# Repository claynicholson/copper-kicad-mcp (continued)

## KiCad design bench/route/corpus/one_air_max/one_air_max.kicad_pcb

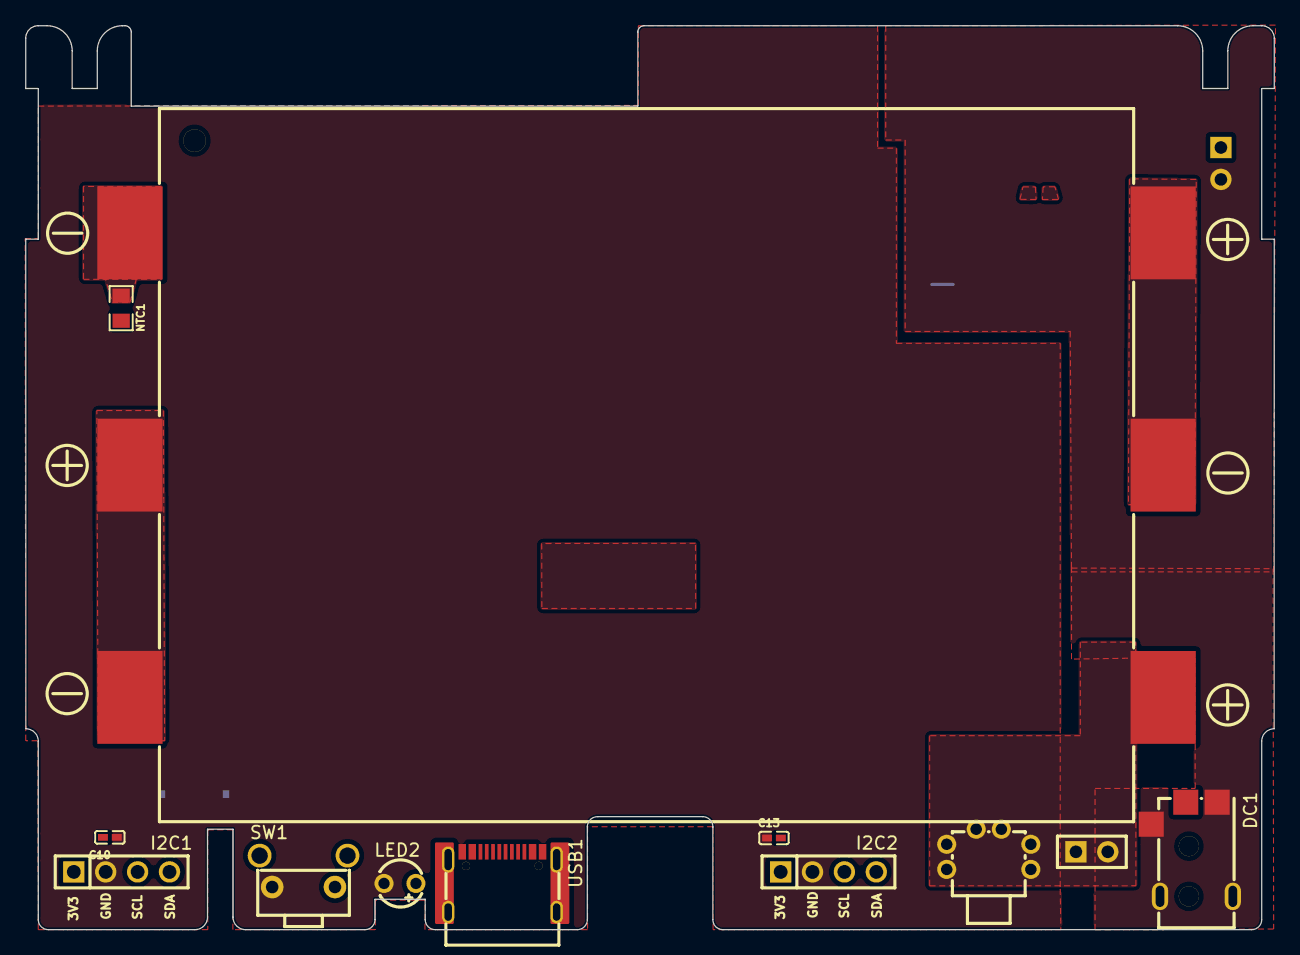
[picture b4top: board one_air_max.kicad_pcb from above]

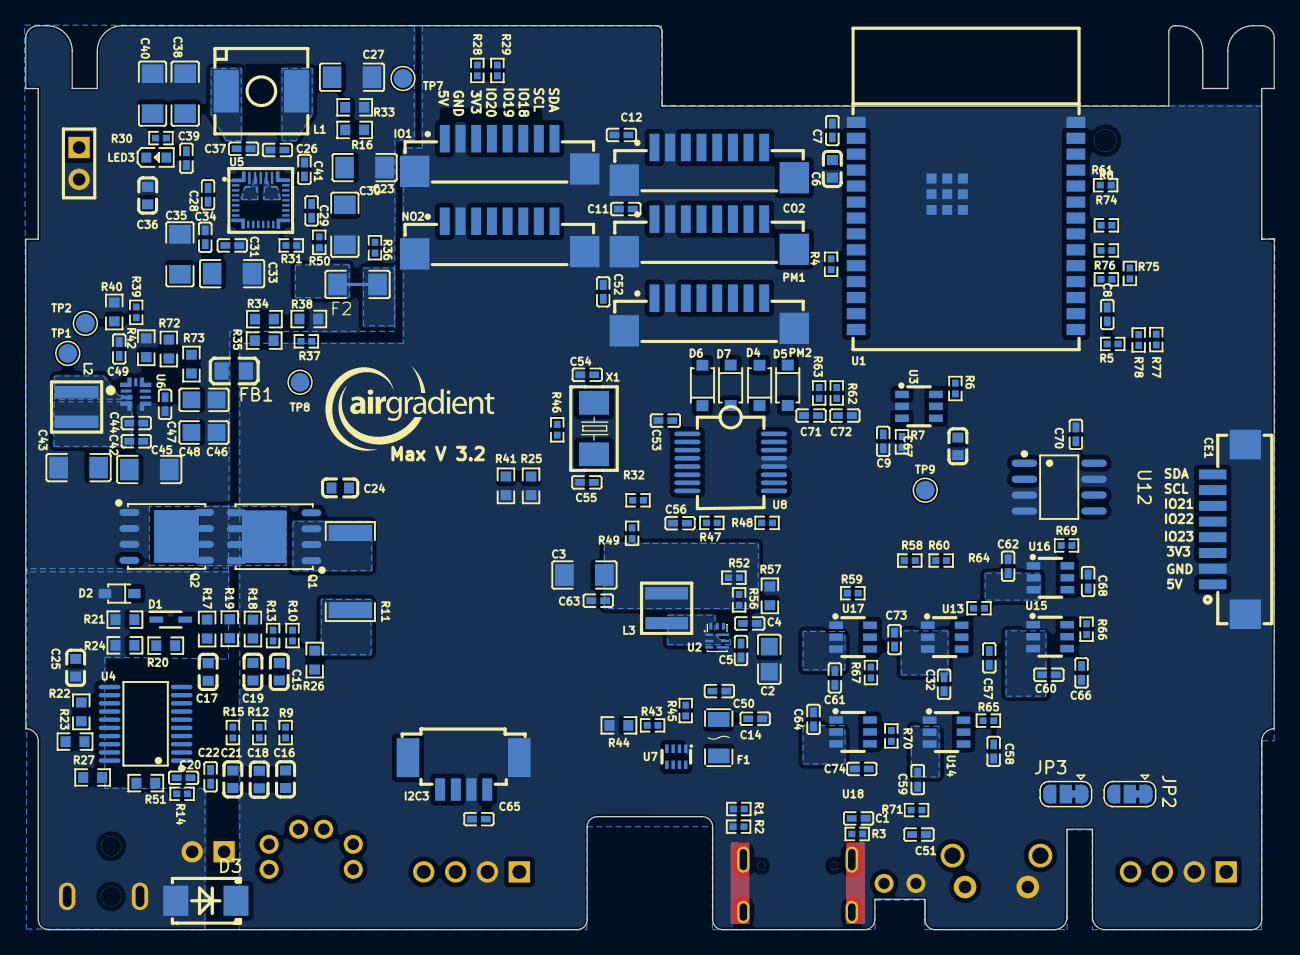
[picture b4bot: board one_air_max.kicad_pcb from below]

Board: 4 copper layers, 99.5 x 72.0 mm, 204 parts (192 on the bottom side), 120 nets, no tracks yet.

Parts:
BAT1: BH-18650-B5BA016; BAT-SMD_BH-18650-B5BA016
Battery1: ZX-PM2.54-1-2PY; HDR-TH_2P-P2.54-V-F
C1, C5, C7, C9, C10, C11, C12, C13, C26, C31, C34, C37, C39, C42, C44, C47, C50, C51, C52, C53, C56, C63, C65, C70: 0.1uF; C0402
C2: 10uF/25V; C0805
C3: 22uF/16V; C1206
C4, C49: 3.3nF; C0402
C6: 22uF; C0603
C8: 10nF; C0402
C14, C57, C58, C68, C74: 22uF; C0402
C15, C16, C17, C18, C19, C21, C24, C25: 0.1uF/50V; C0603
C20, C22: 1uF/50V; C0402
C23, C27, C30, C33, C35, C38, C40, C43, C45: 10uF; C1206
C28, C29: 47nF; C0402
C32, C59, C60, C61, C62, C64: 2.2uF; C0402
C36: 4.7uF; C0603
C41, C71, C72: 1nF; C0402
C46, C48: 22uF; C0805
C54, C55: 22pF_NM; C0402
C66, C73: 1uF; C0402
C67: 500pF; C0603
CE1: HC-1.25-8PWT; CONN-SMD_HC-1.25-8PWT
CO2: HC-1.25-8PLT; CONN-SMD_8P-P1.25_HC-1.25-8PLT
D1: BAS16J_135; SOD2512X80N
D2: MMSZ5246BS-7-F; SOD-323_L1.8-W1.3-LS2.5-RD
D3: SMBJ24A_C908801; SMB_L4.4-W3.6-LS5.3-RD
D4, D5, D6, D7: B5817W_C7420328; SOD-123_L2.7-W1.6-LS3.7-FD
DC1: DC-045A-13A; DC-IN-SMD_DC-045A-13A
F1: 2A-16V; F1206
F2: Fuse 5A; PCB_fuse
FB1: PBY201209T-601Y-N; L0805
I2C1, I2C2: Conn_01x04; HDR-TH_4P-P2.54-V-F
I2C3: 1.25-4PWB; CONN-SMD_1.25-4PWB
IO1: HC-1.25-8PLT; CONN-SMD_8P-P1.25_HC-1.25-8PLT
JP2, JP3: SolderJumper_3_Bridged12; SolderJumper-3_P1.3mm_Bridged12_RoundedPad1.0x1.5mm
L1: SPM6530T-1R0M120; IND-SMD_L7.1-W6.5-P5.60
L2: XGL4020-102MEC; IND-SMD_L4.0-W4.0_XAL4030-332MEC
L3: YSMC0420V-1R0M; IND-SMD_L4.0-W4.0_XGL4020
LED2: XL-304UBC; LED-TH_BD3.8-P2.54-FD_BLUE
LED3: FC-DA1608HRK-620D; LED0603-RD_RED
NO2: HC-1.25-8PLT; CONN-SMD_8P-P1.25_HC-1.25-8PLT
NTC1: KNTC0805/10KF3950; R0805
PM1, PM2: HC-1.25-8PLT; CONN-SMD_8P-P1.25_HC-1.25-8PLT
PWR_SW1: TK-6580A8-1; SW-TH_TK-6580A8-1
Q1, Q2: CSD18534Q5A; PQFN-8_L5.8-W4.9-P1.27-LS6.0-BL
R1, R2, R48: 5.1K; R0402
R3, R6, R31, R37: 100K; R0402
R4, R5, R8, R28, R29, R30, R32, R45, R47, R49, R50, R58, R59, R60, R61, R64, R65, R66, R67, R69, R70, R74, R75, R76, R77, R78: 10K; R0402
R7: 51K; R0402
R9, R12, R14, R15: 1K; R0402
R10, R13, R36: 100; R0402
R11: 10m / 1W; R2512
R16: 10.5K; R0603
R17, R19: 5.1K; R0603
R18: 10M; R0603
R20: 1M; R0603
R21: 3M; R0603
R22: 10K; R0603
R23, R25, R26, R27, R33, R41, R51, R72, R73: 0; R0603
R24: 470K; R0603
R34: 5.23K; R0603
R35: 255K; R0603
R38: 30.1K; R0603
R39: 200K; R0402
R40: 27K; R0603
R42, R57: 7.15K; R0603
R43: 16.9K; R0402
R44: 5K; R0603
R46: 1M; R0402
R52: 113k; R0402
R56: 24.9k; R0402
R62, R63: 22; R0402
R71: 210; R0402
SW1: TS-1096-A1B2-D2; KEY-TH_TS-1096-A1B2-D2
Solarpower1: ZX-PM2.54-1-2PY; HDR-TH_2P-P2.54-V-F
TP1, TP2, TP7, TP8, TP9: T_PG; TestPoint_Pad_D1.5mm
U1: ESP32-C6-WROOM-1-N8; WIRELM-SMD_ESP32-C6-WROOM-1
U2: TPS62902RPJR; VQFN-HR-9_L2.0-W1.5-P0.50-TL
U3: TPL5010DDCR; SOT-23-6_L2.9-W1.6-P0.95-LS2.8-BR
U4: BQ7790512PWR; TSSOP-20_L6.5-W4.4-P0.65-LS6.4-BL
U5: BQ25672RQMR; VQFN-29_L4.0-W4.0-P0.40-BL
U6: TPS62903QRYTRQ1_C20345985; VQFNHR-9_L2.2-W2.0_TPS62993QRYTRQ1
U7: TPS2117DRLR_C22399676; SOT-583-8_L2.1-W1.2-P0.50-LS1.6-BL
U8: WK2132-ISSG; SSOP-16_L7.2-W5.3-P0.65-LS7.8-BL
U12: AT24CM02-SSHD-B; SOIC-8_L4.9-W3.9-P1.27-LS6.0-BL
U13, U14, U15, U16, U17, U18: TPS27081ADDCR; SOT-23-6_L2.9-W1.6-P0.95-LS2.8-BR
USB1: GT-USB-7010ASV; USB-C-SMD_G-SWITCH_GT-USB-7010ASV
X1: SMD-5032_2P 14.7456MHZ 20PF 20PPM; OSC-SMD_L5.0-W3.2

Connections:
+3V3: C3.2, C6.2, C7.2, C9.1, C10.2, C13.2, C53.2, C63.2, C65.2, C66.2, C70.2, C73.2, I2C1.1, I2C2.1, I2C3.1, IO1.3, L3.1, R4.2, R5.2, R6.1, R8.2, R28.2, R29.2, R32.2, R47.2, R48.1, R49.2, R52.2, R66.2, R67.2, R74.2, R75.2, R76.2, R77.2, R78.2, U1.2 (3V3), U2.3 (VOS), U3.1 (VDD), U8.1 (VCC), U12.8 (VCC), U15.4 (VIN), U17.4 (VIN)
+5V: C2.1, C5.2, C14.2, C50.2, C57.2, C58.2, C68.2, C74.2, F1.1, IO1.1, R45.2, R64.2, R65.2, R69.2, R70.2, U2.5 (EN), U2.6 (VIN), U13.4 (VIN), U14.4 (VIN), U16.4 (VIN), U18.4 (VIN)
+5VBAT: C42.2, C43.2, C44.2, C45.2, L2.1, R39.2, U6.3 (VOS), U7.6 (VIN2)
+5VUSB: R43.2, U7.3 (VIN1), U7.5 (MODE), USB1.A4B9 (VBUS), USB1.B4A9 (VBUS)
/A0: R25.1, U8.6 (MP1)
/A1: R41.1, U8.4 (MP3)
/BOOT: C8.2, R5.1, SW1.1, U1.15 (IO9)
/Battery_holder/AVDD: C22.2, R23.2, U4.2 (AVDD)
/Battery_holder/BAT1: BAT1.2, BAT1.4, R9.1
/Battery_holder/BAT2: BAT1.3, BAT1.5, R12.1
/Battery_holder/BAT_TH: NTC1.2, R22.1, U4.15 (TS)
/Battery_holder/CHG: R19.2, U4.13 (CHG)
/Battery_holder/CTRC: R26.1, U4.18 (CTRC)
/Battery_holder/CTRD: R27.2, U4.19 (CTRD)
/Battery_holder/DSG: R17.2, U4.11 (DSG)
/Battery_holder/LD: R24.2, U4.14 (LD)
/Battery_holder/SRN: C17.1, C19.2, R13.2, U4.10 (SRN)
/Battery_holder/SRP: C15.2, C17.2, R10.2, U4.9 (SRP)
/Battery_holder/VBAT+: BAT1.6, C25.2, PWR_SW1.4, PWR_SW1.6, R14.1, R15.1
/EN: C67.2, R6.2, TP9.1, U1.3 (EN), U3.6 (RSTn)
/EN_CE: CE1.5, R61.2, U1.23 (IO15), U15.5 (ON/OFF), U16.5 (ON/OFF)
/EN_CO2: R58.2, U1.5 (IO5), U14.5 (ON/OFF)
/EN_NO2: R59.2, U1.4 (IO4), U17.5 (ON/OFF), U18.5 (ON/OFF)
/EN_PM: R60.2, U1.26 (IO3), U13.5 (ON/OFF)
/I2C_~RST: C56.2, R47.1, U8.8 (#RSTN)
/IO18: IO1.6, R78.1, U1.16 (IO18)
/IO19: IO1.5, R77.1, U1.17 (IO19)
/IO20: IO1.4, R76.1, U1.18 (IO20)
/IO21: CE1.6, R75.1, U1.19 (IO21)
/IO22: R74.1, U1.20 (IO22)
/IO23: CE1.4, R8.1, U1.21 (IO23)
/LED: R71.2, U1.11 (IO10)
/PM1_RXD: D5.2 (K), PM1.5
/PM1_TXD: D4.1 (A), PM1.4
/PM2_RXD: D7.2 (K), PM2.5
/PM2_TXD: D6.1 (A), PM2.4
/PR1: R43.1, R44.2, U7.4 (PR1)
/RX_CE: JP3.1 (A), U1.24 (RXD0)
/RX_CO2: CO2.5, U1.8 (IO0)
/SCL: I2C1.3, I2C2.3, I2C3.3, IO1.7, JP2.3 (B), NO2.7, R28.1, R32.1, U1.6 (IO6), U5.14 (SCL), U8.5 (MP2), U12.6 (SCL)
/SCL_TXD: CE1.7, JP2.2 (C)
/SDA: I2C1.4, I2C2.4, I2C3.4, IO1.8, JP3.3 (B), NO2.8, R29.1, R49.1, U1.7 (IO7), U5.15 (SDA), U8.7 (MP0), U12.5 (SDA)
/SDA_RXD: CE1.8, JP3.2 (C)
/Solar_module/BTST1: C28.2, U5.4 (BTST1)
/Solar_module/BTST2: C29.2, U5.19 (BTST2)
/Solar_module/FB/VSET: R39.1, R40.2, TP2.1, U6.9 (FB/VSET)
/Solar_module/ILIM_HIZ: R35.2, R37.2, U5.17 (ILIM_HIZ)
/Solar_module/PROG: R16.2, U5.20 (PROG)
/Solar_module/REGN: C36.2, R34.1, R35.1, U5.5 (REGN)
/Solar_module/SW1: C28.1, L1.1, U5.28 (SW1)
/Solar_module/SW2: C29.1, L1.2, U5.26 (SW2)
/Solar_module/SYS: C26.2, C27.2, R72.1, TP7.1, U5.25 (SYS)
/Solar_module/Solar+: C31.2, C33.2, C34.2, C35.2, D3.1, DC1.1, R30.1, Solarpower1.1, U5.2 (VBUS), U5.3 (VBUS), U5.8 (VAC2), U5.9 (VAC1)
/Solar_module/VBAT: Battery1.1, C23.2, C30.2, F2.1, R36.2, R73.1, TP8.1, U5.22 (BAT), U5.23 (BAT)
/TX_CE: JP2.1 (A), U1.25 (TXD0)
/TX_CO2: CO2.4, U1.9 (IO1)
/USB+: R63.2, U1.14 (IO13)
/USB-: R62.2, U1.13 (IO12)
/USB_D+: C71.2, R63.1, USB1.A6 (DP1), USB1.B6 (DP2)
/USB_D-: C72.2, R62.1, USB1.A7 (DN1), USB1.B7 (DN2)
/VMUX: F1.2, U7.2 (VOUT), U7.7 (VOUT)
/VOUT1: C11.2, C32.2, C52.2, PM1.1, PM2.1, U13.2 (VOUT), U13.3 (VOUT)
/VOUT2: C12.2, C59.2, CO2.1, U14.2 (VOUT), U14.3 (VOUT)
/VOUT3: C60.2, CE1.3, U15.2 (VOUT), U15.3 (VOUT)
/VOUT4: C62.2, CE1.1, U16.2 (VOUT), U16.3 (VOUT)
/VOUT5: C61.2, NO2.3, U17.2 (VOUT), U17.3 (VOUT)
/VOUT6: C64.2, NO2.1, U18.2 (VOUT), U18.3 (VOUT)
/WD_RST: U1.27 (IO2), U3.4 (DONE)
BAT-: BAT1.1, C15.1, C16.1, C18.1, C19.1, C20.1, C21.1, C22.1, NTC1.1, R10.1, R11.1, R26.2, R27.1, R51.1, U4.8 (AVSS), U4.20 (DVSS)
GND: C1.1, C2.2, C3.1, C4.1, C5.1, C6.1, C7.1, C8.1, C9.2, C10.1, C11.1, C12.1, C13.1, C14.1, C32.1, C50.1, C51.1, C52.1, C53.1, C54.1, C55.1, C56.1, C57.1, C58.1, C59.1, C60.1, C61.1, C62.1, C63.1, C64.1, C65.1, C66.1, C67.1, C68.1, C70.1, C71.1, C72.1, C73.1, C74.1, CE1.2, CE1.9, CE1.10, CO2.2, CO2.10, FB1.1, I2C1.2, I2C2.2, I2C3.2, I2C3.5, IO1.2, IO1.9, IO1.10, LED2.2 (K), NO2.2, NO2.9, NO2.10, PM1.2, PM1.10, PM2.2, PM2.9, PM2.10, R1.1, R2.1, R3.1, R7.1, R25.2, R41.2, R44.1, R56.1, R57.1, R58.1, R59.1, R60.1, R61.1, SW1.2, U1.1 (GND), U1.28 (GND), U1.29 (GND), U1.30 (GND), U1.31 (GND), U1.32 (GND), U1.33 (GND), U1.34 (GND), U1.35 (GND), U1.36 (GND), U1.37 (GND), U2.4 (GND), U3.2 (GND), U7.1 (GND), U8.12 (GND), U8.13 (MD0), U12.3 (A2), U12.4 (GND), U12.7 (WP), U13.1 (R2), U14.1 (R2), U15.1 (R2), U16.1 (R2), U17.1 (R2), U18.1 (R2), USB1.A1B12 (GND), USB1.B1A12 (GND)
unnamed: C1.2, R3.2, USB1.1 (SHELL), USB1.2 (SHELL), USB1.3 (SHELL), USB1.4 (SHELL)
unnamed: C24.2, Q1.1 (S), Q1.2 (S), Q1.3 (S), R11.2, R13.1, R18.1
unnamed: D1.2, R19.1, R20.2
unnamed: D1.1, D2.1 (K), Q2.4 (G), R20.1, R21.2
unnamed: D4.2 (K), U8.15 (TX1)
unnamed: D5.1 (A), U8.16 (RX1)
unnamed: D6.2 (K), U8.10 (TX2)
unnamed: D7.1 (A), U8.11 (RX2)
unnamed: F2.2, PWR_SW1.2, PWR_SW1.5
unnamed: C51.2, LED2.1 (A), R71.1
unnamed: LED3.2 (A), R30.2
unnamed: LED3.1 (K), U5.1 (STAT)
unnamed: Q1.5 (D), Q1.6 (S), Q1.7 (S), Q1.8 (S), Q2.5 (D), Q2.6 (S), Q2.7 (S), Q2.8 (S)
unnamed: Q1.4 (G), R17.1, R18.2
unnamed: R16.1, R33.1
unnamed: R4.1, U1.10 (IO8)
unnamed: R52.1, R56.2, U2.9 (FB/VSET)
unnamed: R57.2, U2.7 (MODE/S-CONF)
unnamed: C4.2, U2.8 (SS/TR)
unnamed: L3.2, U2.2 (SW)
unnamed: R7.2, U3.3 (DELAY/M_RST)
unnamed: R23.1, R51.2, U4.17 (CCFG)
unnamed: C16.2, R9.2, U4.7 (VC1)
unnamed: C18.2, R12.2, U4.6 (VC2)
unnamed: C21.2, R15.2, U4.3 (VC5), U4.4 (VC4), U4.5 (VC3)
unnamed: C20.2, R14.2, U4.1 (VDD)
unnamed: R22.2, U4.16 (VTB)
unnamed: R36.1, U5.18 (BATP)
unnamed: R31.1, U5.13 (CE)
unnamed: C37.2, C38.2, C39.2, C40.2, U5.29 (PMID)
unnamed: C41.1, U5.24 (SDRV)
unnamed: R34.2, R38.1, R50.2, U5.16 (TS)
unnamed: C46.2, C47.2, C48.2, R72.2, R73.2, U6.5 (EN), U6.6 (VIN)
unnamed: R42.2, U6.7 (MODE/S-CONF)
unnamed: TP1.1, U6.1 (PG)
unnamed: C49.2, U6.8 (SS/TR)
unnamed: L2.2, U6.2 (SW)
unnamed: R45.1, U7.8 (ST)
unnamed: R48.2, U8.9 (#IRQ)
unnamed: C54.2, R46.2, U8.2 (OSCI), X1.2 (OSC2)
unnamed: C55.2, R46.1, U8.3 (OSCO), X1.1 (OSC1)
unnamed: R64.1, U13.6 (R1/C1)
unnamed: R65.1, U14.6 (R1/C1)
unnamed: R66.1, U15.6 (R1/C1)
unnamed: R69.1, U16.6 (R1/C1)
unnamed: R67.1, U17.6 (R1/C1)
unnamed: R70.1, U18.6 (R1/C1)
unnamed: R1.2, USB1.A5 (CC1)
unnamed: R2.2, USB1.B5 (CC2)
PGND: Battery1.2, C23.1, C24.1, C25.1, C26.1, C27.1, C30.1, C31.1, C33.1, C34.1, C35.1, C36.1, C37.1, C38.1, C39.1, C40.1, C41.2, C42.1, C43.1, C44.1, C45.1, C46.1, C47.1, C48.1, C49.1, D2.2 (A), D3.2, DC1.2, DC1.3, DC1.4, FB1.2, Q2.1 (S), Q2.2 (S), Q2.3 (S), R21.1, R24.1, R31.2, R33.2, R37.1, R38.2, R40.1, R42.1, R50.1, Solarpower1.2, U5.10 (ACDRV2), U5.11 (ACDRV1), U5.27 (GND), U6.4 (GND)

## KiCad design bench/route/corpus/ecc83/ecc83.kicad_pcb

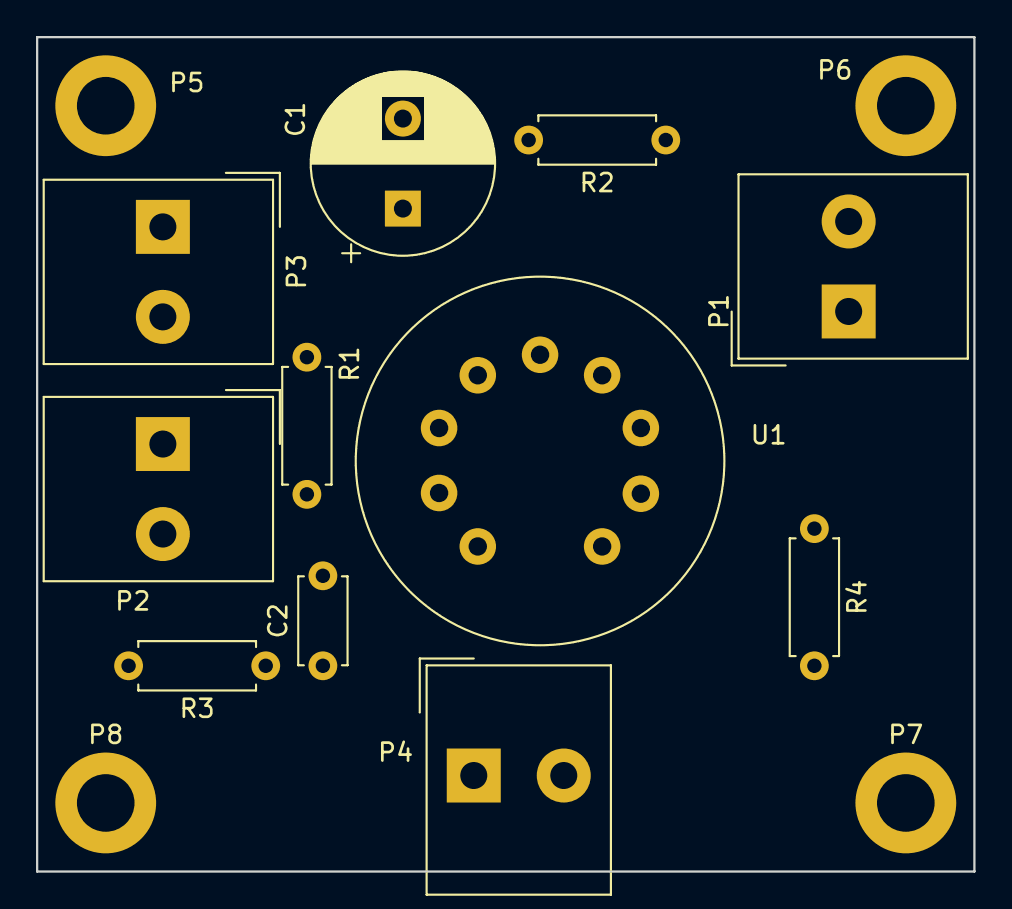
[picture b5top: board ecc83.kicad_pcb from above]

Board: 2 copper layers, 52.1 x 46.4 mm, 15 parts (0 on the bottom side), 9 nets, no tracks yet.

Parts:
C1: 10uF; CP_Radial_D10.0mm_P5.00mm
C2: 680nF; C_Disc_D4.7mm_W2.5mm_P5.00mm
P1: IN; Altech_AK300_1x02_P5.00mm_45-Degree
P2: OUT; Altech_AK300_1x02_P5.00mm_45-Degree
P3: POWER; Altech_AK300_1x02_P5.00mm_45-Degree
P4: CONN_2; Altech_AK300_1x02_P5.00mm_45-Degree
P5, P6, P7, P8: MOUNTING_HOLE; MountingHole_3.2mm_M3_DIN965_Pad
R1, R2: 1.5K; R_Axial_DIN0207_L6.3mm_D2.5mm_P7.62mm_Horizontal
R3: 100K; R_Axial_DIN0207_L6.3mm_D2.5mm_P7.62mm_Horizontal
R4: 47K; R_Axial_DIN0207_L6.3mm_D2.5mm_P7.62mm_Horizontal
U1: ECC83; Valve_ECC-83-1

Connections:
GND: C1.2, P1.1, P2.2 (PM), P3.2 (PM), R2.2, R3.2, R4.2
unnamed: P1.2 (PM), R4.1, U1.2 (G)
unnamed: C2.1, P2.1, R3.1
unnamed: C1.1, P3.1, U1.6 (A)
unnamed: P4.1, U1.9 (F2)
unnamed: P4.2 (PM), U1.4 (F1), U1.5 (F1)
unnamed: R1.1, U1.1 (A), U1.7 (G)
unnamed: C2.2, R1.2, U1.8 (K)
unnamed: R2.1, U1.3 (K)

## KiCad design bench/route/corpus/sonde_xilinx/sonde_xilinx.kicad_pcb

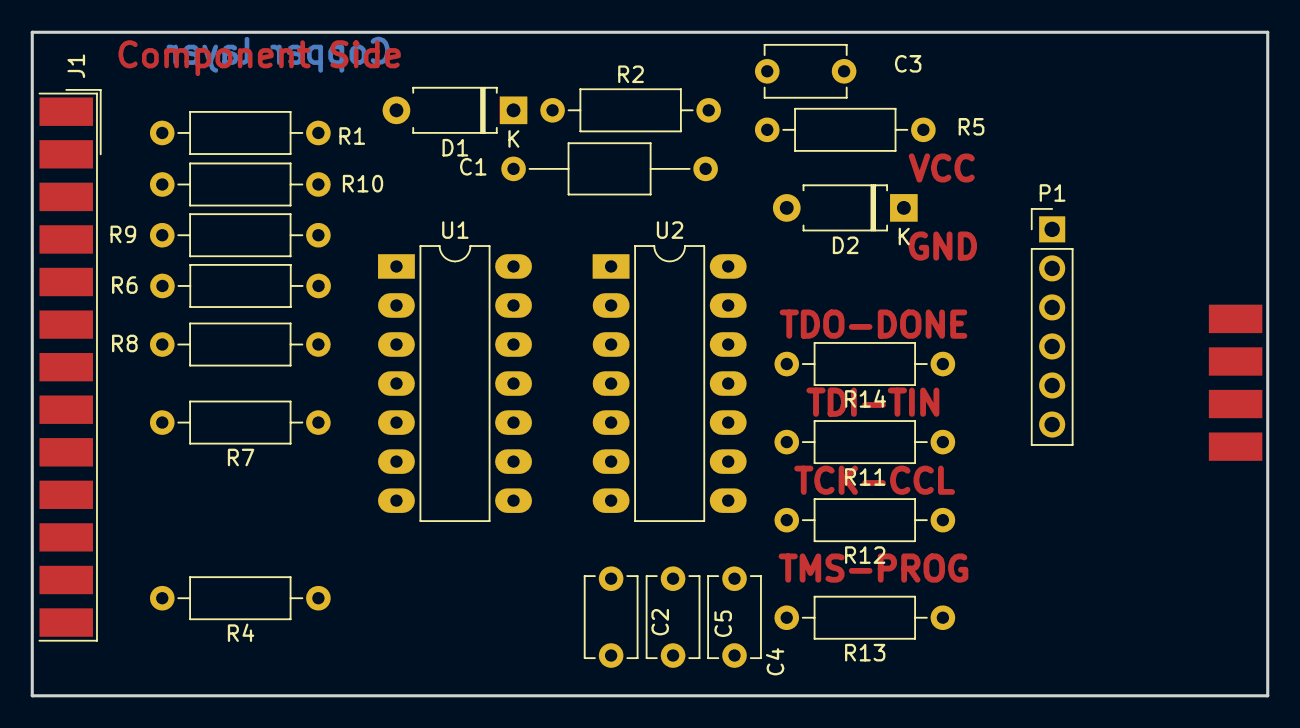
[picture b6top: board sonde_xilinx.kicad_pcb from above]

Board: 2 copper layers, 80.4 x 43.2 mm, 25 parts (1 on the bottom side), 26 nets, no tracks yet.

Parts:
C1: 1uF; C_Axial_L5.1mm_D3.1mm_P12.50mm_Horizontal
C2, C3, C4, C5: 100pF; C_Disc_D5.1mm_W3.2mm_P5.00mm
D1, D2: BAT46; D_A-405_P7.62mm_Horizontal
J1: DB25MALE; DSUB-25_Male_EdgeMount_P2.77mm
J2: DB9MALE; DSUB-9_Male_EdgeMount_P2.77mm
P1: CONN_6; PinHeader_1x06_P2.54mm_Vertical
R1, R6, R7, R8, R9, R10, R11, R12, R13, R14: 100; R_Axial_DIN0207_L6.3mm_D2.5mm_P10.16mm_Horizontal
R2: 5,1K; R_Axial_DIN0207_L6.3mm_D2.5mm_P10.16mm_Horizontal
R4: 47; R_Axial_DIN0207_L6.3mm_D2.5mm_P10.16mm_Horizontal
R5: 1K; R_Axial_DIN0207_L6.3mm_D2.5mm_P10.16mm_Horizontal
U1, U2: 74LS125; DIP-14_W7.62mm_LongPads

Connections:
/CLK-D1: J1.3, R10.2
/CTRL-D3: J1.5, R8.2
/DONE-SELECT*: J1.13, R4.2
/PWR_3,3-5V: D2.1 (A), J2.1, P1.1
/TCK-CCLK: J2.4, P1.5, R12.1
/TD0-DONE: J2.2, P1.3, R14.1
/TD0-PROG-D4: J1.6, R6.2
/TDI-DIN: J2.3, P1.4, R11.1
/TDI-DIN-D0: J1.2, R7.2
/TMS-PROG: J2.5, P1.6, R13.1
/TMS-PROG-D2: J1.4, R9.2
/VCC_SENSE-ERROR*: J1.15, R1.2
GND: C1.2, C2.2, C3.2, C4.2, C5.2, J1.20, J1.25, J2.6, J2.7, J2.8, J2.9, P1.2, R5.2, U1.2 (D), U1.7 (GND), U2.1 (E), U2.4 (E), U2.5 (D), U2.7 (GND), U2.9 (D), U2.10 (E), U2.12 (D), U2.13 (E)
unnamed: D1.2 (K), R1.1
unnamed: J1.8, J1.11, J1.12
unnamed: R6.1, U1.1 (E)
unnamed: C3.1, R2.2, R14.2, U1.3 (O), U2.2 (D)
unnamed: R7.1, U1.5 (D)
unnamed: R8.1, U1.4 (E), U1.10 (E), U1.13 (E)
unnamed: C2.1, R11.2, U1.6 (O)
unnamed: R10.1, U1.9 (D)
unnamed: C5.1, R12.2, U1.8 (O)
unnamed: R9.1, U1.12 (D)
unnamed: C4.1, R13.2, U1.11 (O)
unnamed: R4.1, U2.3 (O)
VCC: C1.1, D1.1 (A), D2.2 (K), R2.1, R5.1, U1.14 (VCC), U2.14 (VCC)

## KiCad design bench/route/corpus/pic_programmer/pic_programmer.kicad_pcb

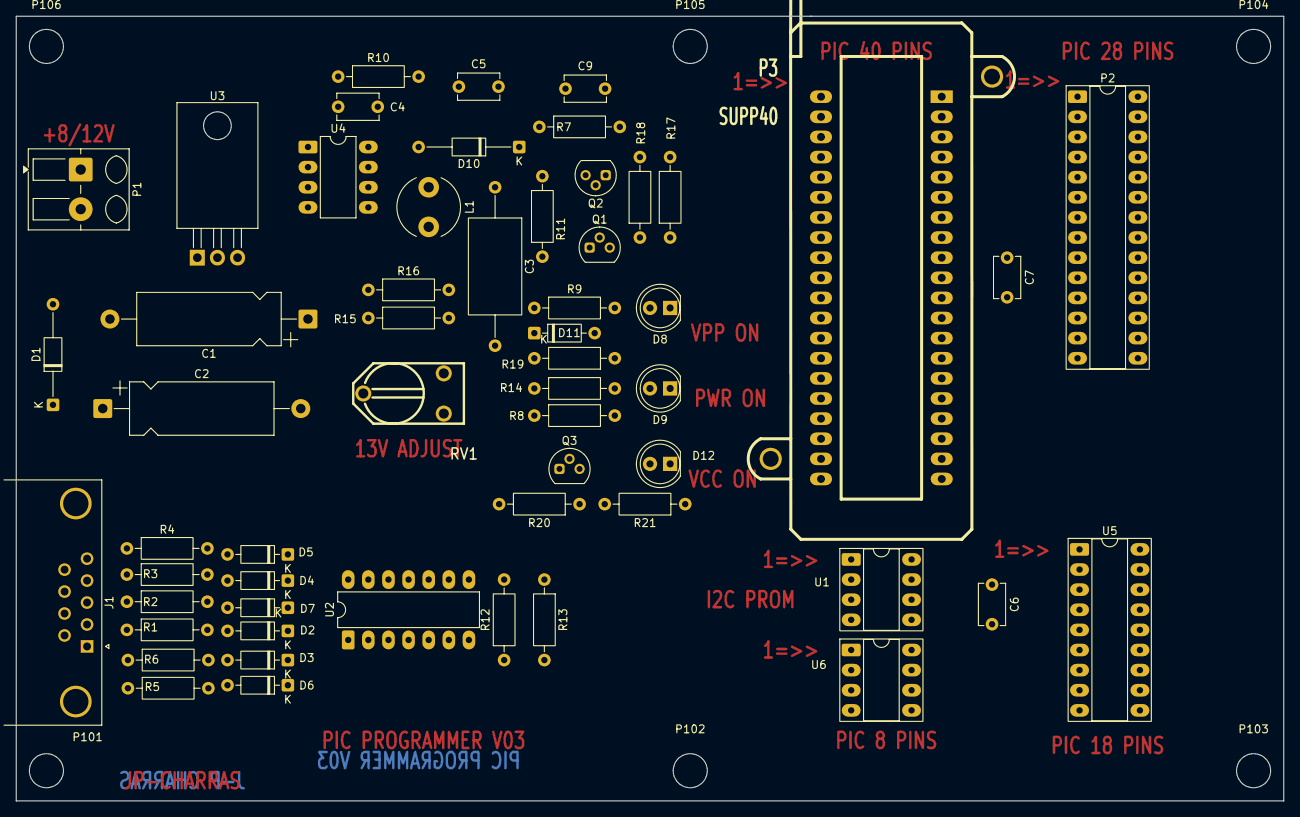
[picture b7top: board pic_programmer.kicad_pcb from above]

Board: 2 copper layers, 160.0 x 99.1 mm, 63 parts (1 on the bottom side), 34 nets, no tracks yet.

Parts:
C1: 100µF; CP_Axial_L18.0mm_D6.5mm_P25.00mm_Horizontal
C2: 220uF; CP_Axial_L18.0mm_D6.5mm_P25.00mm_Horizontal
C3: 22uF/25V; C_Axial_L12.0mm_D6.5mm_P20.00mm_Horizontal
C4: 0; C_Disc_D5.1mm_W3.2mm_P5.00mm
C5: 10nF; C_Disc_D5.1mm_W3.2mm_P5.00mm
C6, C7: 100nF; C_Disc_D5.1mm_W3.2mm_P5.00mm
C9: 220nF; C_Disc_D5.1mm_W3.2mm_P5.00mm
D1: 1N4004; D_DO-35_SOD27_P12.70mm_Horizontal
D2, D3, D4, D5, D6, D7, D11: BAT43; D_DO-35_SOD27_P7.62mm_Horizontal
D8: RED-LED; LED_D5.0mm
D9: GREEN-LED; LED_D5.0mm
D10: SCHOTTKY; D_DO-35_SOD27_P12.70mm_Horizontal
D12: YELLOW-LED; LED_D5.0mm
J1: DB9-FEMAL; DSUB-9_Socket_Horizontal_P2.77x2.84mm_EdgePinOffset7.70mm_H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
JP1: JUMPER; SolderJumper-2_P1.3mm_Open_TrianglePad1.0x1.5mm
L1: 22uH; L_Radial_D7.8mm_P5.00mm_Fastron_07HCP
P1: CONN_2; Altech_AK300_1x02_P5.00mm_45-Degree
P2: SUPP28; DIP-28_W7.62mm_Socket_LongPads
P3: SUPP40; 40tex-Ell600
P101, P102, P103, P104, P105, P106: CONN_1; MountingHole_4.3mm_M4
Q1: BC237; TO-92
Q2, Q3: BC307; TO-92
R1, R2, R3, R4, R5, R6, R7: 10K; R_Axial_DIN0207_L6.3mm_D2.5mm_P10.16mm_Horizontal
R8: 1K; R_Axial_DIN0207_L6.3mm_D2.5mm_P10.16mm_Horizontal
R9, R19, R20: 2.2K; R_Axial_DIN0207_L6.3mm_D2.5mm_P10.16mm_Horizontal
R10: 5,1K; R_Axial_DIN0207_L6.3mm_D2.5mm_P10.16mm_Horizontal
R11, R17: 22K; R_Axial_DIN0207_L6.3mm_D2.5mm_P10.16mm_Horizontal
R12, R13, R14, R21: 470; R_Axial_DIN0207_L6.3mm_D2.5mm_P10.16mm_Horizontal
R15: 6.2K; R_Axial_DIN0207_L6.3mm_D2.5mm_P10.16mm_Horizontal
R16: 62K; R_Axial_DIN0207_L6.3mm_D2.5mm_P10.16mm_Horizontal
R18: 220; R_Axial_DIN0207_L6.3mm_D2.5mm_P10.16mm_Horizontal
RV1: 1K; RV2X4
U1: 24Cxx; DIP-8_W7.62mm_Socket_LongPads
U2: 74HC125; DIP-14_W7.62mm_LongPads
U3: 7805; TO-220-3_Horizontal_TabDown
U4: LT1373; DIP-8_W7.62mm_LongPads
U5: PIC_18_PINS; DIP-18_W7.62mm_Socket_LongPads
U6: PIC_8_PINS; DIP-8_W7.62mm_Socket_LongPads

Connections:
/CLOCK-RB6: P2.27, P3.39, R13.2, U1.6 (SCL), U5.12 (ICSPC/RB6), U6.6 (GP1)
/DATA-RB7: P2.28, P3.40, R12.2, U1.5 (SDA), U2.12, U5.13 (ICSPD/RB7), U6.7 (GP0)
/PC-CLOCK-OUT: J1.7, R5.1, R6.1
/PC-DATA-IN: J1.8, U2.11
/PC-DATA-OUT: J1.4, R3.1, R4.1
/VPP_ON: J1.3, R1.1, R2.1
/VPP/MCLR: P2.1, P3.1, R18.2, U5.4 (MCLR), U6.4 (GP3/MCLR)
/pic_sockets/VCC_PIC: C6.1, C7.1, JP1.2, P2.20, P3.11, P3.32, Q3.1 (C), R21.2, U1.8 (VCC), U5.14 (VDD), U6.1 (VDD)
GND: C1.2, C2.2, C3.2, C4.2, C5.2, C6.2, C7.2, D3.2 (A), D5.2 (A), D7.2 (A), D8.1 (K), D9.1 (K), D12.1 (K), J1.5, P1.1, P2.8, P2.19, P3.8, P3.12, P3.31, Q1.3 (E), R2.2, R4.2, R6.2, R15.2, R17.2, U1.1 (A0), U1.2 (A1), U1.3 (A2), U1.4 (GND), U2.1, U2.4, U2.7 (GND), U2.10, U2.13, U3.2 (GND), U4.6 (GND_S), U4.7 (GND), U5.5 (VSS), U6.8 (VSS)
unnamed: C5.1, R10.2
unnamed: D1.2 (A), P1.2 (PM)
unnamed: C2.1, D1.1 (K), U3.1 (VI)
unnamed: D2.2 (A), D3.1 (K), R1.2, U2.2
unnamed: D4.2 (A), D5.1 (K), R3.2, U2.5
unnamed: D6.2 (A), D7.1 (K), R5.2, U2.9
unnamed: D8.2 (A), R9.2
unnamed: D9.2 (A), R14.2
unnamed: D10.2 (A), L1.1, U4.8 (Vsw)
unnamed: D11.2 (A), R19.1
unnamed: D11.1 (K), Q1.1 (C), R11.1
unnamed: D12.2 (A), R21.1
unnamed: Q1.2 (B), R8.2
unnamed: C9.2, Q2.2 (B), R7.2, R11.2
unnamed: Q2.1 (C), R9.1, R17.1, R18.1
unnamed: Q3.2 (B), R19.2, R20.2
unnamed: R8.1, U2.3
unnamed: R12.1, U2.6
unnamed: R13.1, U2.8
unnamed: R15.1, RV1.1
unnamed: R16.1, RV1.3
unnamed: RV1.2, U4.2 (FB+)
unnamed: C4.1, R10.1, U4.1 (Vc)
VCC: C1.1, D2.1 (K), D4.1 (K), D6.1 (K), JP1.1, L1.2, Q3.3 (E), R14.1, R20.1, U2.14 (VCC), U3.3 (VO), U4.5 (Vin)
VPP: C3.1, C9.1, D10.1 (K), Q2.3 (E), R7.1, R16.2

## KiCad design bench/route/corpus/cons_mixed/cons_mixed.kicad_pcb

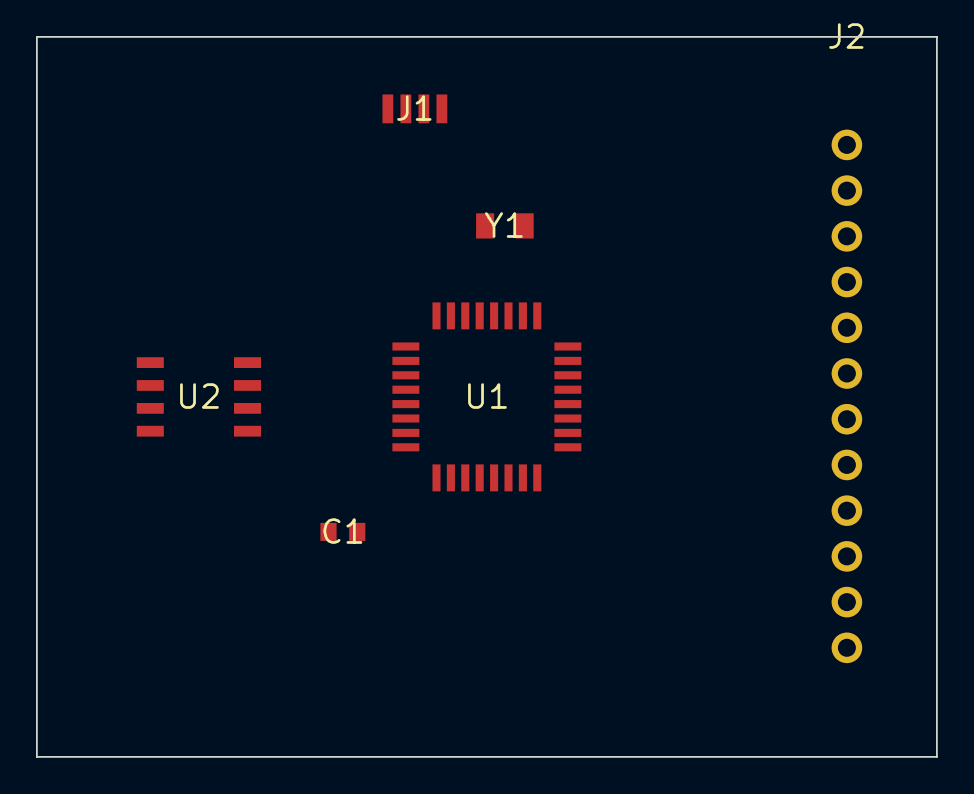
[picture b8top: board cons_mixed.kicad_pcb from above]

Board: 4 copper layers, 50.0 x 40.0 mm, 6 parts (0 on the bottom side), 24 nets, no tracks yet.

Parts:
C1: C1; FP_C1
J1: J1; FP_J1
J2: J2; FP_J2
U1: U1; FP_U1
U2: U2; FP_U2
Y1: Y1; FP_Y1

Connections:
+3V3: C1.1, U1.4, U1.26, U2.5
/P0: J2.12, U1.14
/P1: J2.11, U1.15
/P2: J2.10, U1.16
/P3: J2.9, U1.17
/P4: J2.8, U1.18
/P5: J2.7, U1.19
/P6: J2.6, U1.20
/P7: J2.5, U1.21
/P8: J2.4, U1.22
/P9: J2.3, U1.23
/P10: J2.2, U1.24
/P11: J2.1, U1.25
/Q_CLK: U1.2, U2.7
/Q_CS: U1.5, U2.1
/Q_IO0: U1.1, U2.8
/Q_IO1: U1.6, U2.2
/Q_IO2: U1.7, U2.3
/Q_IO3: U1.3, U2.6
/USB_D_N: J1.3, U1.10
/USB_D_P: J1.2, U1.9
/XI: U1.12, Y1.1
/XO: U1.13, Y1.2
GND: C1.2, J1.4, U1.8, U1.11, U1.27, U2.4

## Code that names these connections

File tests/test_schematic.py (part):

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    pins = [{"number": "1", "name": "VBUS", "alternates": []},
            {"number": "2", "name": "~{RESET}", "alternates": []},
            {"number": "3", "name": "IO20/RXD", "alternates": []},
            {"number": "4", "name": "PA9", "alternates": ["USART1_TX", "TIM1_CH2"]},
            {"number": "5", "name": "PB6", "alternates": ["USART1_TX", "I2C1_SCL"]},
            {"number": "6", "name": "GND", "alternates": []},
            {"number": "7", "name": "GND", "alternates": []},
            {"number": "8", "name": "PA10", "alternates": ["USART1_RX"]}]
    assert [p["number"] for p in G.match_pins(pins, "1")[0]] == ["1"]
    assert G.match_pins(pins, "VBUS")[1] == "name"
    assert G.match_pins(pins, "vbus")[1] == "name-ci"
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    {"op": "connect", "pins": ["ren.2", "cen.1", "U1.EN"], "net": "EN"},
    {"op": "connect", "pins": ["J1.CC1", "rcc1.1"], "net": "CC1"},
    {"op": "connect", "pins": ["J1.CC2", "rcc2.1"], "net": "CC2"},
    {"op": "connect", "pins": ["J1.D+", "U1.IO19"], "net": "USB_DP"},
    {"op": "connect", "pins": ["J1.D-", "U1.IO18"], "net": "USB_DN"},
    {"op": "connect", "pins": ["U1.IO8", "rled.1"], "net": "LED_DRV"},
    {"op": "connect", "pins": ["rled.2", "led.A"], "net": "LED_A"},
    {"op": "no_connect", "pins": ["J1.SBU1", "J1.SBU2", "U1.IO0", "U1.IO1", "U1.IO2", "U1.IO3", "U1.IO4", "U1.IO5",
                                  "U1.IO6", "U1.IO7", "U1.IO9", "U1.IO10", "U1.TXD", "U1.RXD"]},
    {"op": "pwr_flag", "net": "GND"},
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    assert "4 hierarchical/global" in r["connectivity"] and "1 PWR_FLAG" in r["connectivity"], r["connectivity"]
    assert full() == before                        # the WHOLE hierarchy, not only the isolated sub-sheet
    sch = Schematic.load(pr.dir / "pic_sockets.kicad_sch")
    assert {l["net"] for l in sch.labels() if l["kind"] == "hierarchical"} == {"VCC_PIC", "VPP-MCLR", "CLOCK-RB6", "DATA-RB7"}
    assert _flags(pr.dir / "pic_sockets.kicad_sch") == 1
    assert not _wiring_errors(pr), [(v["type"], v["description"]) for v in _wiring_errors(pr)]

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
def test_delete_label_kind_filter_and_rename_net():
    pr = _demo("pic_programmer", "pic_lbl")
    r = O.apply_ops(pr, [{"op": "delete", "label": "VPP-MCLR", "kind": "local"}], sheet="pic_sockets", dry_run=True)
    assert r["changed"][0].startswith("deleted 4 label(s)") and not r["warnings"], r
    r = O.apply_ops(pr, [{"op": "delete", "label": "VPP-MCLR"}], sheet="pic_sockets", dry_run=True)
    assert "1 hierarchical" in r["changed"][0] and any("parent sheet's pin" in w for w in r["warnings"]), r
    r = O.apply_ops(pr, [{"op": "rename_net", "from": "CLOCK-RB6", "to": "CLK_RB6"}], sheet="pic_sockets", dry_run=True)
    assert "renamed net CLOCK-RB6 → CLK_RB6 (6 label(s))" in r["changed"][0] and len(r["warnings"]) == 1, r
    assert _code(lambda: O.apply_ops(pr, [{"op": "rename_net", "from": "CLOCK-RB6", "to": "DATA-RB7"}],
                                     sheet="pic_sockets", dry_run=True)) == "NET_CONFLICT"
    # joining an existing hierarchical net uses a local label (no extra sheet-interface label)
    O.apply_ops(pr, [{"op": "place", "lib_id": "Device:R", "id": "r"}, {"op": "connect", "pin": "r.1", "net": "VCC_PIC"},
                     {"op": "connect", "pin": "r.2", "net": "VPP-MCLR"}], sheet="pic_sockets")
    sch = Schematic.load(pr.dir / "pic_sockets.kicad_sch")
    assert sum(1 for l in sch.labels() if l["kind"] == "hierarchical") == 4
    pn = N.pin_nets(N.export_netlist(pr))
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    r = O.apply_ops(pr, [{"op": "place", "lib_id": "Device:R", "value": "2.2k", "id": "r", "near": "U201", "footprint": R06},
                         {"op": "place", "lib_id": "Device:LED", "id": "led"},
                         {"op": "connect", "pin": "r.1", "net": "VCC"}, {"op": "connect", "pin": "led.K", "net": "GND"},
                         {"op": "connect", "pins": ["r.2", "led.A"], "net": "LED_A"}], sheet="ampli_ht.kicad_sch")
    assert r["refs"] == {"r": "R214", "led": "D205"}, r["refs"]
    assert any("R314" in c for c in r["changed"]), r["changed"]
    assert any("wired as LED_A" in c for c in r["changed"]), r["changed"]
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                         {"op": "place", "lib_id": "Device:LED", "id": "led", "near": "mcu"},
                         {"op": "place", "lib_id": "Device:R", "value": "330", "id": "rl", "near": "led"},
                         {"op": "connect", "pins": ["mcu.PB0", "rl.1"], "net": "LED_DRV"},
                         {"op": "connect", "pins": ["rl.2", "led.A"], "net": "LED_A"},
                         {"op": "connect", "pins": ["led.K", "mcu.GND"], "net": "GND"},
                         {"op": "connect", "pin": "mcu.VCC", "net": "+5V"}])
    assert any("wired as LED_A" in c for c in r["changed"]), r["changed"]
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
def test_text_width_matches_kicad_stroke_font():
    """The old estimate was ~20 % short (0.78 × size per capital; KiCad draws ~0.95), so label room was
    under-reserved and labels of stacked parts met end to end ('BOOTSEL USB_DP'). Measured on kicad-cli plots:
    'BOOTSEL' ≈ 7.9 mm, 'USB_DP' ≈ 6.8 mm at 1.27 mm text."""
    from copper_kicad.sch.model import text_width
    assert 7.6 < text_width("BOOTSEL") < 8.3, text_width("BOOTSEL")
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    O.apply_ops(pr, [{"op": "place", "lib_id": "Device:R", "id": "a", "value": "27"},
                     {"op": "place", "lib_id": "Device:R", "id": "b", "value": "1k"},
                     {"op": "place", "lib_id": "Device:R", "id": "c", "value": "1k"},
                     {"op": "connect", "pin": "a.1", "net": "USB_CONN_DP"}, {"op": "connect", "pin": "a.2", "net": "USB_DP"},
                     {"op": "connect", "pin": "b.1", "net": "BOOTSEL"}, {"op": "connect", "pin": "b.2", "net": "QSPI_SS"},
                     {"op": "connect", "pin": "c.1", "net": "USB_CONN_DN"}, {"op": "connect", "pin": "c.2", "net": "USB_DM"}])
    boxes = [(l["net"], LAY.label_box(l)) for l in Schematic.load(pr.sch).labels()]
    for i in range(len(boxes)):
        for j in range(i + 1, len(boxes)):
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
